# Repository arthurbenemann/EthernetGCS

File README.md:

EthernetGCS - Ground Control Station with Ethernet port
==========

Required Toolchain:
- GIT
- MPLAB IDE v1.51
- Compiler XC16 v1.1
- Microchip Application Libraries v2012/10/15

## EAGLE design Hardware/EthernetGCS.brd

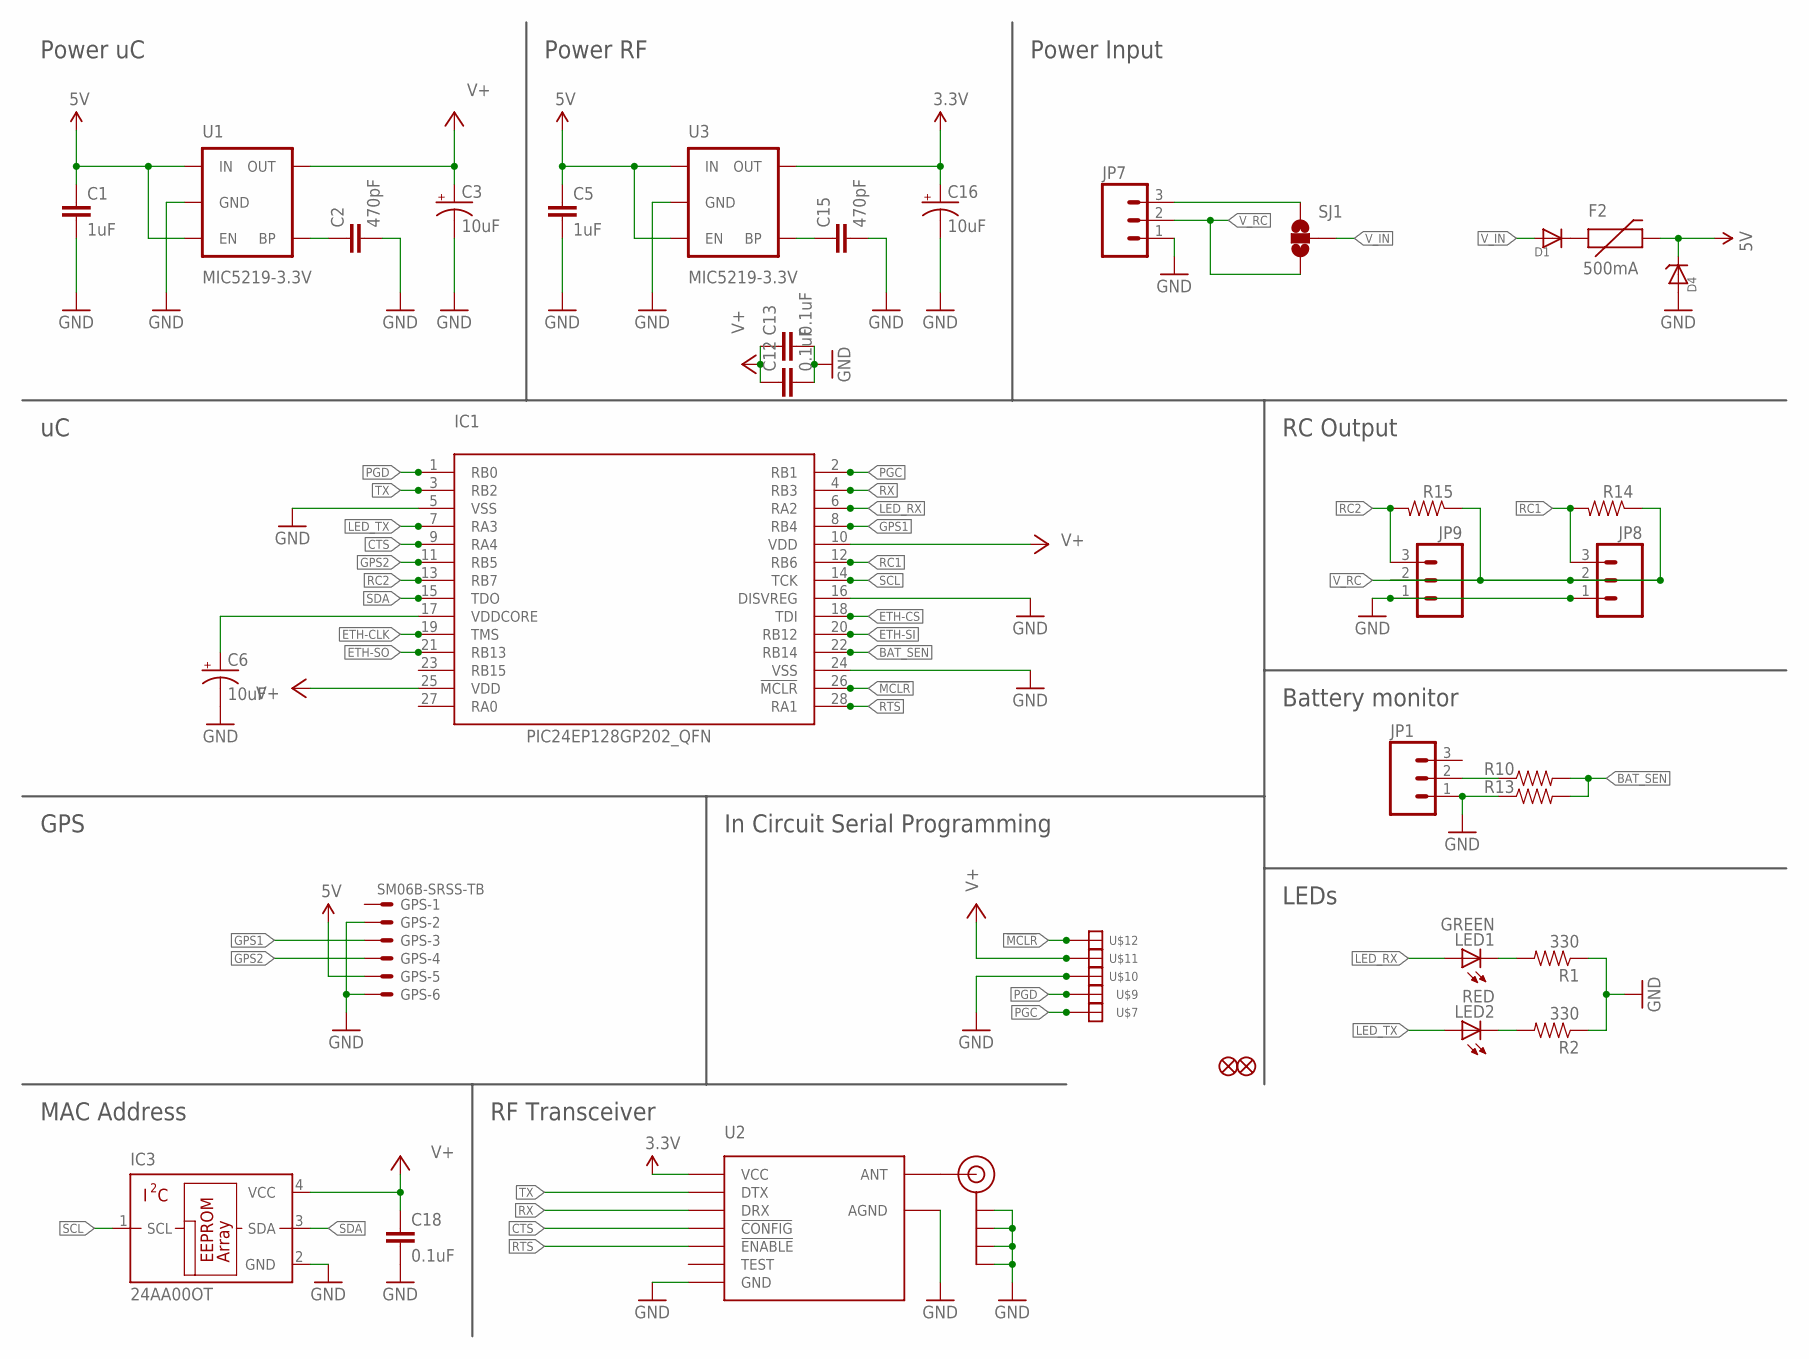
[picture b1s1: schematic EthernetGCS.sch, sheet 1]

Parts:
C1, C5: 1uF; 0402-CAP
C2, C15: 470pF; 0402-CAP
C3, C6, C16: 10uF; EIA3216
C12, C13, C18: 0.1uF; 0402-CAP
D1: MBR120VLSFT1G; SOD-123
D4: MMSZ5233BT1G; SOD-123
F2: 500mA; PTC-1206
GPS: SM06B-SRSS-TB
IC1: PIC24EP128GP202_QFN; QFN28-ML_6X6MM; MPN PIC24FJ64GA002-E/ML
IC3: 24AA00OT; SOT23-5L
J$1: SMA_EDGE; SMA-EDGE
JP1, JP7, JP8, JP9: M03PTH; 1X03
JP2, JP3: FIDUCIAL1X2; FIDUCIAL-1X2
LED1: GREEN; LED-0603
LED2: RED; LED-0603
R1, R2: 330; 0402-RES
R10, R13, R14, R15: RESISTOR0402-RES; 0402-RES
SJ1: SOLDERJUMPER_2WAYT; SJ_2
U1, U3: MIC5219-3.3V; SOT23-5
U2: HM-TRPSMD; HM-TRP-SMD
U$7, U$9, U$10, U$11, U$12: SOLDER_PAD150_75; SOLD_PAD_150_75

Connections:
3.3V: C16.A (+), U2.VCC, U3.5 (OUT)
5V: C1.1, C5.1, D4.C, F2.2, GPS.5, U1.1 (IN), U1.3 (EN), U3.1 (IN), U3.3 (EN)
!MCLR: IC1.26 (!MCLR), U$12.P$1
BAT_SEN: IC1.22 (RB14), R10.2, R13.2
CTS: IC1.9 (RA4), U2.!CONFIG
ETH-CLK: IC1.19 (TMS); also elsewhere on the board
ETH-CS: IC1.18 (TDI); also elsewhere on the board
ETH-SI: IC1.20 (RB12); also elsewhere on the board
ETH-SO: IC1.21 (RB13); also elsewhere on the board
GND: C1.2, C2.2, C3.C (-), C5.2, C6.C (-), C12.2, C13.2, C15.2, C16.C (-), C18.2, D4.A, GPS.2, GPS.6, IC1.5 (VSS), IC1.16 (DISVREG), IC1.24 (VSS), IC3.2 (GND), J$1.GND@0 (GND), J$1.GND@1 (GND), J$1.GND@2 (GND), J$1.GND@3 (GND), JP1.1, JP7.1, JP8.1, JP9.1, R1.1, R2.1, R13.1, U1.2 (GND), U2.AGND, U2.GND, U3.2 (GND), U$10.P$1; also elsewhere on the board
GPS1: GPS.3, IC1.8 (RB4)
GPS2: GPS.4, IC1.11 (RB5)
LED_RX: IC1.6 (RA2), LED1.A
LED_TX: IC1.7 (RA3), LED2.A
unnamed: J$1.SIG (SIGNAL), U2.ANT
unnamed: C2.1, U1.4 (BP)
unnamed: C15.1, U3.4 (BP)
unnamed: C6.A (+), IC1.17 (VDDCORE)
unnamed: D1.C, F2.1
unnamed: LED1.C, R1.2
unnamed: LED2.C, R2.2
unnamed: JP7.3, SJ1.3
unnamed: JP1.2, R10.1
PGC: IC1.2 (RB1), U$7.P$1
PGD: IC1.1 (RB0), U$9.P$1
RC1: IC1.12 (RB6), JP8.3, R14.2
RC2: IC1.13 (RB7), JP9.3, R15.2
RTS: IC1.28 (RA1), U2.!ENABLE
RX: IC1.4 (RB3), U2.DRX
SCL: IC1.14 (TCK), IC3.1 (SCL)
SDA: IC1.15 (TDO), IC3.3 (SDA)
TX: IC1.3 (RB2), U2.DTX
V+: C3.A (+), C12.1, C13.1, C18.1, IC1.10 (VDD), IC1.25 (VDD), IC3.4 (VCC), U1.5 (OUT), U$11.P$1; also elsewhere on the board
V_IN: D1.A, SJ1.2
V_RC: JP7.2, JP8.2, JP9.2, R14.1, R15.1, SJ1.1

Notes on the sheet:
Power uC
Power RF
MAC Address
RF Transceiver
RC Output
LEDs
Power Input
Battery monitor
GPS
In Circuit Serial Programming

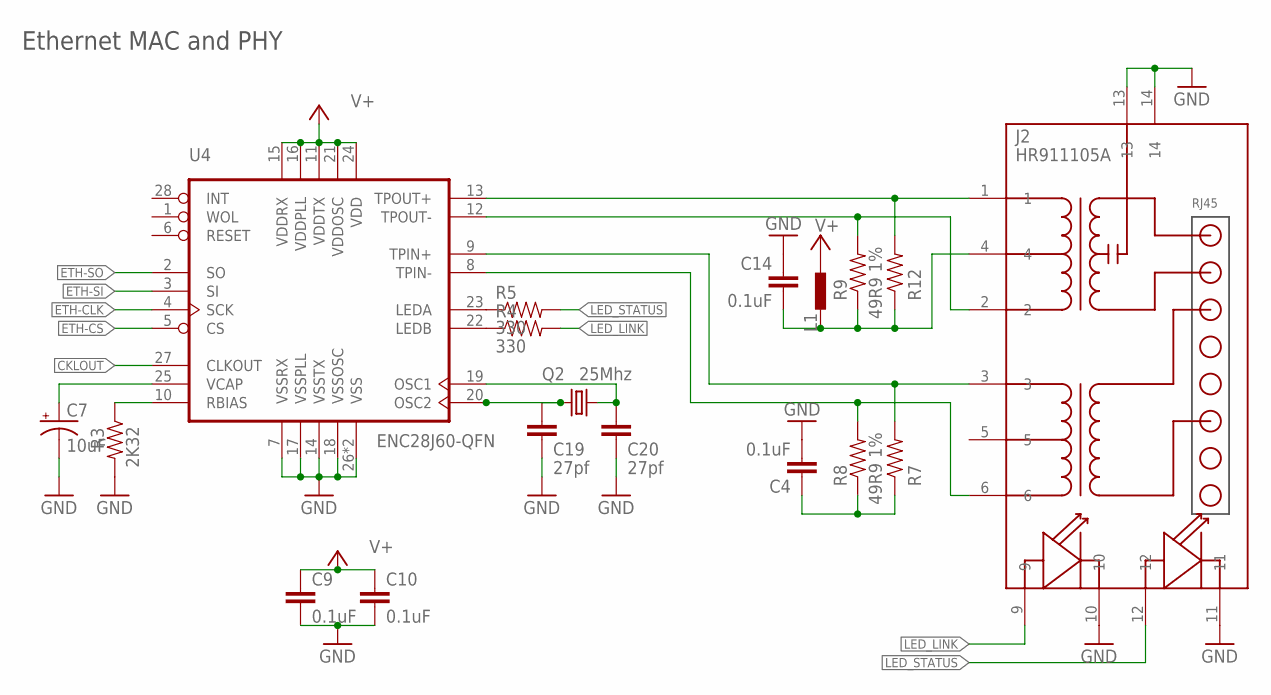
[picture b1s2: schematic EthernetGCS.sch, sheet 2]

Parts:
C4, C9, C10, C14: 0.1uF; 0402-CAP
C7: 10uF; EIA3216
C19, C20: 27pf; 0402-CAP
J2: HR911105A
L1: BLM15HD102SN1; 0402-IND
Q2: 25Mhz; CTS406
R3: 2K32; 0402-RES
R4, R5: 330; 0402-RES
R7, R8, R9, R12: 49R9 1%; 0402-RES
U4: ENC28J60-QFN; QFN28

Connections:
CCT: C14.2, J2.4, L1.P$1 (1), R9.1, R12.1
CKLOUT: U4.27 (CLKOUT)
ETH-CLK: U4.4 (SCK); also elsewhere on the board
ETH-CS: U4.5 (CS); also elsewhere on the board
ETH-SI: U4.3 (SI); also elsewhere on the board
ETH-SO: U4.2 (SO); also elsewhere on the board
GND: C4.2, C7.C (-), C9.2, C10.2, C14.1, C19.2, C20.2, J2.10, J2.11, J2.13, J2.14, R3.2, U4.7 (VSSRX), U4.14 (VSSTX), U4.17 (VSSPLL), U4.18 (VSSOSC), U4.26 (VSS), U4.EXP (VSS); also elsewhere on the board
LED_LINK: J2.9, R4.2
LED_STATUS: J2.12, R5.2
unnamed: C7.A (+), U4.25 (VCAP)
unnamed: C19.1, Q2.1, U4.20 (OSC2)
unnamed: C20.1, Q2.3 (2), U4.19 (OSC1)
unnamed: R3.1, U4.10 (RBIAS)
unnamed: R5.1, U4.23 (LEDA)
unnamed: R4.1, U4.22 (LEDB)
unnamed: C4.1, R7.1, R8.1
RD+: J2.3, R7.2, U4.9 (TPIN+)
RD-: J2.6, R8.2, U4.8 (TPIN-)
TD+: J2.1, R12.2, U4.13 (TPOUT+)
TD-: J2.2, R9.2, U4.12 (TPOUT-)
V+: C9.1, C10.1, L1.P$2 (2), U4.11 (VDDTX), U4.15 (VDDRX), U4.16 (VDDPLL), U4.21 (VDDOSC), U4.24 (VDD); also elsewhere on the board

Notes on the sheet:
Ethernet MAC and PHY

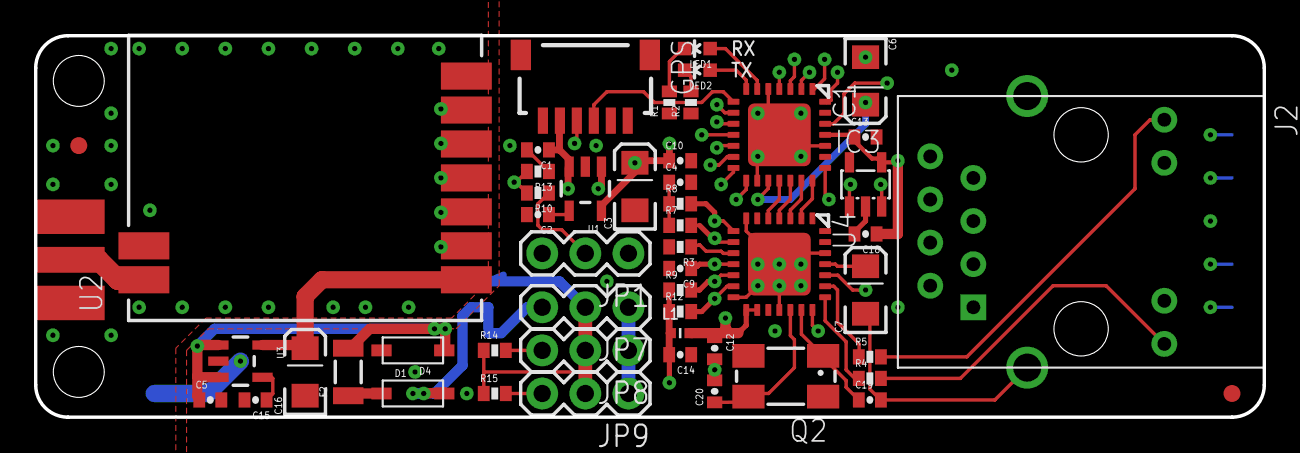
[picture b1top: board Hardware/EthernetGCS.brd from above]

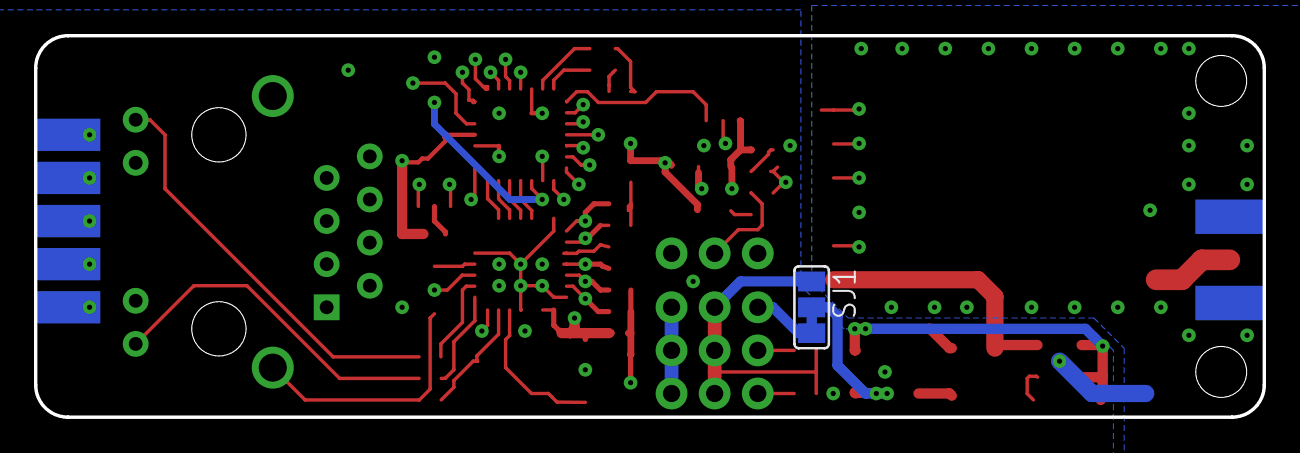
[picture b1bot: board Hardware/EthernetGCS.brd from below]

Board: 4 copper layers, 72.4 x 22.5 mm, 58 parts (6 on the bottom side), 49 nets.

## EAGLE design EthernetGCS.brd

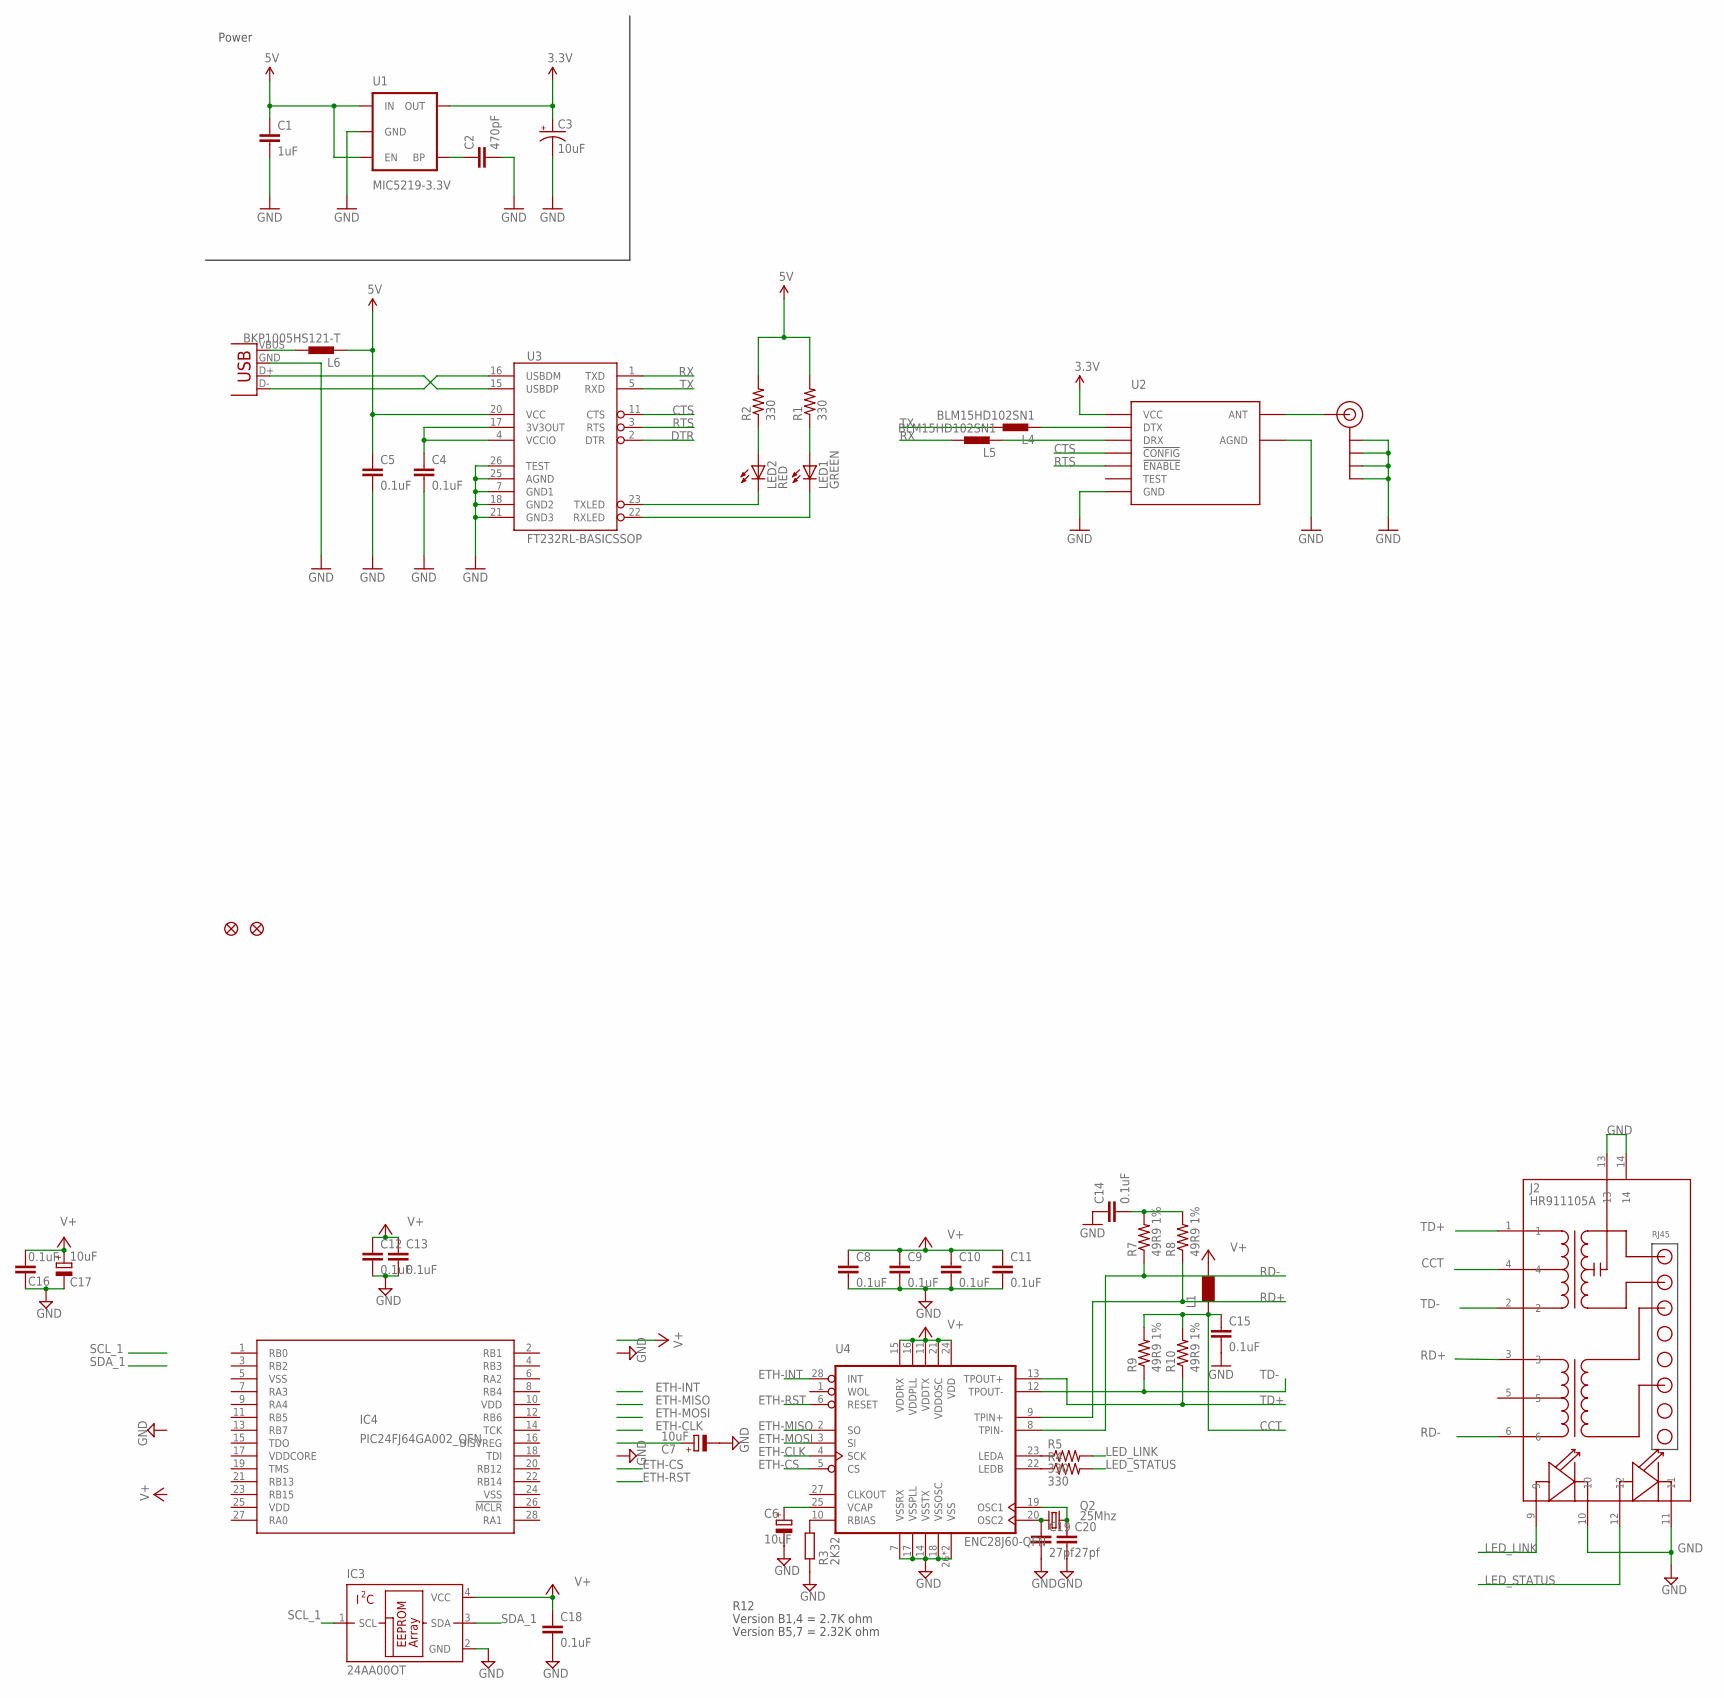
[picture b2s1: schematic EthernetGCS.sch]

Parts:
C1: 1uF; 0402-CAP
C2: 470pF; 0402-CAP
C3: 10uF; EIA3216
C4, C5, C8, C9, C10, C11, C12, C13, C14, C15, C18: 0.1uF; 0402-CAP
C6, C7, C17: 10uF; SMC_A
C16: 0.1uF; C0805
C19, C20: 27pf; 0402-CAP
IC3: 24AA00OT; SOT23-5L
IC4: PIC24FJ64GA002_QFN; QFN28-ML_6X6MM
J2: HR911105A
J$1: SMA_EDGE; SMA-EDGE
JP1, JP2: FIDUCIAL1X2; FIDUCIAL-1X2
L1: WE-KIL_0805; WE-KI_0805_B
L4, L5: BLM15HD102SN1; 0402-IND
L6: BKP1005HS121-T; 0402-IND
LED1: GREEN; LED-0603
LED2: RED; LED-0603
Q2: 25Mhz; CTS406
R1, R2, R4, R5: 330; 0402-RES
R3: 2K32; R0805
R7, R8, R9, R10: 49R9 1%; 0402-RES
U1: MIC5219-3.3V; SOT23-5
U2: HM-TRPSMD; HM-TRP-SMD
U3: FT232RL-BASICSSOP; SSOP28DB
U4: ENC28J60-QFN; QFN28
X1: USB-A-H

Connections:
3.3V: C3.A (+), U1.5 (OUT), U2.VCC
5V: C1.1, C5.1, L6.P$2 (2), R1.2, R2.2, U1.1 (IN), U1.3 (EN), U3.20 (VCC)
CCT: C15.1, J2.4, L1.2 (1), R9.2, R10.2
CTS: U2.!CONFIG, U3.11 (CTS)
DTR: U3.2 (DTR)
ETH-CLK: U4.4 (SCK)
ETH-CS: U4.5 (CS)
ETH-INT: U4.28 (INT)
ETH-MISO: U4.2 (SO)
ETH-MOSI: U4.3 (SI)
ETH-RST: U4.6 (RESET)
GND: C1.2, C2.2, C3.C (-), C4.2, C5.2, C6.-, C7.-, C8.2, C9.2, C10.2, C11.2, C12.2, C13.2, C14.1, C15.2, C16.2, C17.-, C18.2, C19.2, C20.2, IC3.2 (GND), J2.10, J2.11, J2.13, J2.14, J$1.GND@0 (GND), J$1.GND@1 (GND), J$1.GND@2 (GND), J$1.GND@3 (GND), R3.1, U1.2 (GND), U2.AGND, U2.GND, U3.7 (GND1), U3.18 (GND2), U3.21 (GND3), U3.25 (AGND), U3.26 (TEST), U4.7 (VSSRX), U4.14 (VSSTX), U4.17 (VSSPLL), U4.18 (VSSOSC), U4.26 (VSS), U4.EXP (VSS), X1.GND (VBUS)
LED_LINK: J2.9, R5.2
LED_STATUS: J2.12, R4.2
unnamed: J$1.SIG (SIGNAL), U2.ANT
unnamed: C2.1, U1.4 (BP)
unnamed: C4.1, U3.4 (VCCIO), U3.17 (3V3OUT)
unnamed: L4.P$2 (2), U2.DTX
unnamed: U3.15 (USBDP), X1.D+ (D-)
unnamed: U3.16 (USBDM), X1.D- (D+)
unnamed: L5.P$2 (2), U2.DRX
unnamed: LED2.A, R2.1
unnamed: LED1.A, R1.1
unnamed: LED2.C, U3.23 (TXLED)
unnamed: LED1.C, U3.22 (RXLED)
unnamed: L6.P$1 (1), X1.VBUS (GND)
unnamed: C6.+, U4.25 (VCAP)
unnamed: C19.1, Q2.1, U4.20 (OSC2)
unnamed: C20.1, Q2.3 (2), U4.19 (OSC1)
unnamed: R3.2, U4.10 (RBIAS)
unnamed: R5.1, U4.23 (LEDA)
unnamed: R4.1, U4.22 (LEDB)
unnamed: C14.2, R7.2, R8.2
RD+: J2.3, R8.1, U4.9 (TPIN+)
RD-: J2.6, R7.1, U4.8 (TPIN-)
RTS: U2.!ENABLE, U3.3 (RTS)
RX: L5.P$1 (1), U3.1 (TXD)
SCL_1: IC3.1 (SCL)
SDA_1: IC3.3 (SDA)
TD+: J2.1, R10.1, U4.13 (TPOUT+)
TD-: J2.2, R9.1, U4.12 (TPOUT-)
TX: L4.P$1 (1), U3.5 (RXD)
V+: C8.1, C9.1, C10.1, C11.1, C12.1, C13.1, C16.1, C17.+, C18.1, IC3.4 (VCC), L1.1 (2), U4.11 (VDDTX), U4.15 (VDDRX), U4.16 (VDDPLL), U4.21 (VDDOSC), U4.24 (VDD)
VDD: IC4.10 (VDD), IC4.25 (VDD)
VDDCORE: IC4.17 (VDDCORE)
VSS: IC4.5 (VSS), IC4.24 (VSS)

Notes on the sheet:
Power
Version B1,4 = 2.7K ohm
Version B5,7 = 2.32K ohm
R12

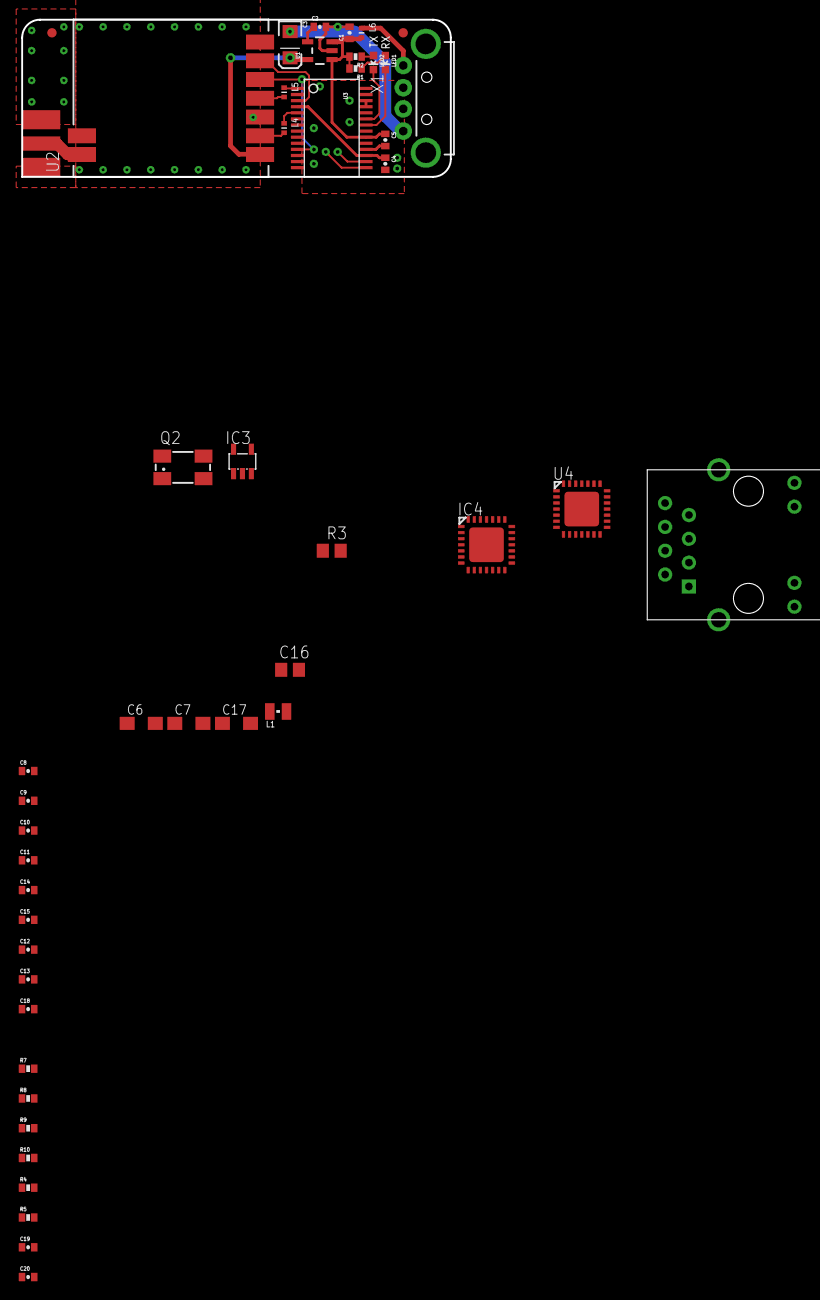
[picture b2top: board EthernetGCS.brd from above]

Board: 4 copper layers, 45.7 x 16.8 mm, 47 parts (0 on the bottom side), 36 nets.

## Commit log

2013-03-03 Adding Files from 3D Robotics
2013-03-03 Renaming files
2013-03-03 Adding Ethernet IC, a PIC 24F and a RJ45 connector.
2013-03-03 Cloning 3DR board, to use as reference.
2013-03-03 Moving board files to a new folder.
2013-03-03 Cleaning the schematic
2013-03-03 Splitting the schematic into two sheets
2013-03-03 Changing the RC connectors for the one in the SparkFun library
2013-03-03 Adding information to the RC section
2013-03-03 Organizing the schematic
2013-03-03 Adding a sense line for the batterie
2013-03-03 Fix the problem of multiple ground symbols
2013-03-04 Just moving some parts to easy layout process.
2013-03-04 Adding firmware for the project.
    This is just a prototype that runs on a picDev board with a ENC28J60 ethernet adapter.
2013-03-04 Refactoring Hardware definitions in the firmware.
2013-03-04 Connecting the power pins of the uC.
2013-03-04 Refactoring the Serial2TCP file.
2013-03-04 Adding suport for two TCP connections
2013-03-04 Better implementation of the multiple TCP connections code
2013-03-04 Now the Serial2TCP bridge transmist every received byte from the serial to all the TCP sockets
2013-03-04 Modification on the led blinking style, to be able to measure the performance of the TCP2Serial routine.
2013-03-04 Adding a 3D model for the Board
2013-03-04 Enable Open Drain pins to suport 5V on TX output.
2013-03-05 Suport for RC servos.
2013-03-05 Adding GPS port, RC output pull-ups. Connecting stuff, and changing parts positions.
2013-03-05 Layout: tracing tracks.
2013-03-05 Continuing the board layout, adding connections to the schematic
2013-03-05 More Layout, and designing the power section of the board
2013-03-05 Analysem system current consumption
2013-03-05 More Layout...
2013-03-05 Updating the 3D model with the new layout.
2013-03-06 More layout. Deleting reference board, adding ground planes.
2013-03-06 Layout is finished.
    Or at least is seams that way.
2013-03-06 Organizing the schematic, small modifications to the PCB.
2013-03-06 Updating the 3D model.

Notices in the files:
parts and their libraries:
SparkFun-Connectors: Licensing: CC v3.0 Share-Alike You are welcome to use this library for commercial purposes.
